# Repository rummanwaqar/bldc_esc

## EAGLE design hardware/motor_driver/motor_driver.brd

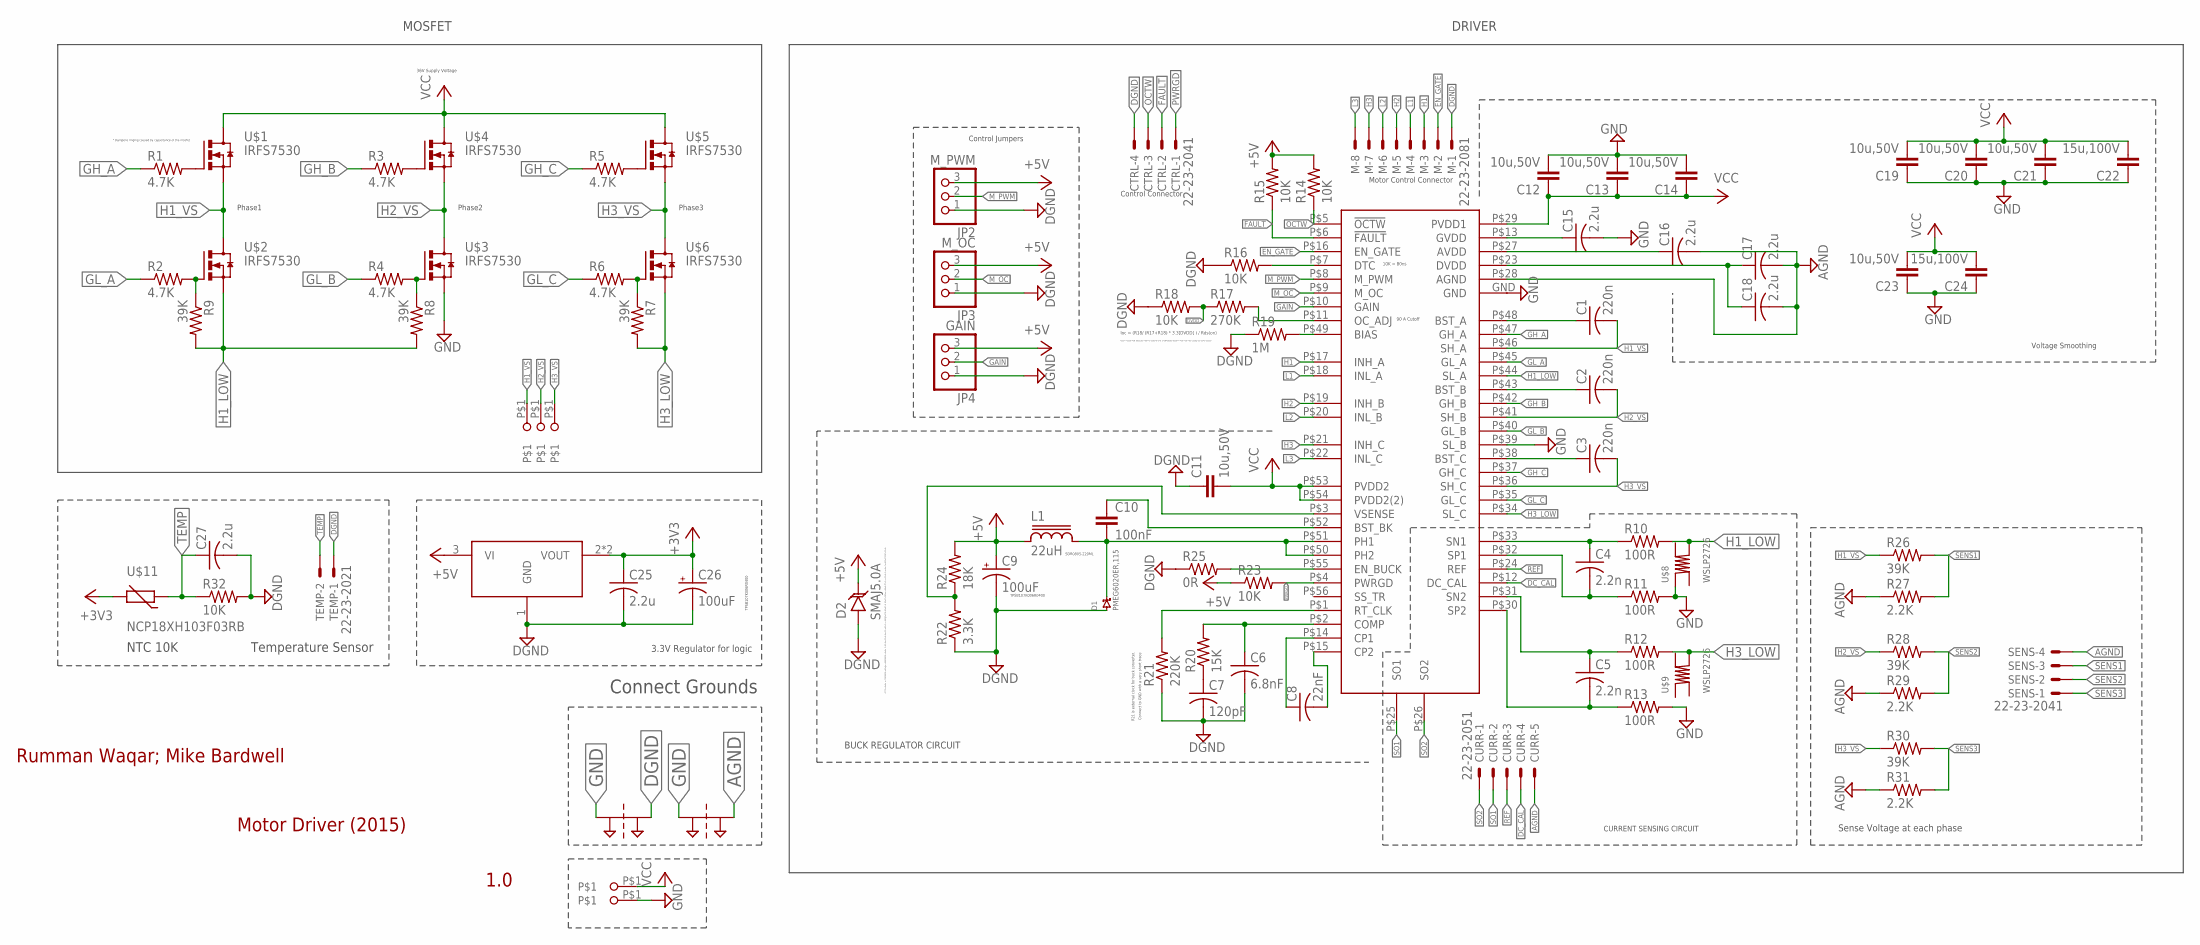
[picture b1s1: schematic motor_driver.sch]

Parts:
C1, C2, C3: 220n; C0805
C4, C5: 2.2n; C0603
C6: 6.8nF; C0603
C7: 120pF; C0603
C8: 22nF; C0603
C9, C26: 100uF; EIA3528-KIT
C10: 100nF; 0805
C11, C12, C13, C14, C19, C20, C21, C23: 10u,50V; 1206
C15, C16, C17, C18, C25, C27: 2.2u; C0805
C22, C24: 15u,100V; C2220K
CTRL: 22-23-2041
CURR: 22-23-2051
D1: PMEG6020ER,115; SOD123W
D2: SMAJ5.0A; SMA-DIODE
JP2: M_PWM; 1X03
JP3: M_OC; 1X03
JP4: GAIN; 1X03
L1: 22uH; SDR0805
M: 22-23-2081
PT1, PT2: 2PT_GND_TIE
R1, R2, R3, R4, R5, R6: 4.7K; R0603
R7, R8, R9: 39K; R0603
R10, R11, R12, R13: 100R; R0603
R14, R15, R16, R18, R23: 10K; R0603
R17: 270K; R0603
R19: 1M; R0603
R20: 15K; R0603
R21: 220K; R0603
R22: 3.3K; R0603
R24: 18K; R0603
R25: 0R; R0603
R26, R28, R30: 39K; R0805
R27, R29, R31: 2.2K; R0805
R32: 10K; M0805
SENS: 22-23-2041
TEMP: 22-23-2021
U$1, U$2, U$3, U$4, U$5, U$6: IRFS7530; IRF7530_HEATSINK
U$7: DRV8302
U$8, U$9: WSLP2726
U$10: TC2117; SOT223
U$11: NCP18XH103F03RB; R0603
U$12, U$13, U$14, U$15, U$16: 1CONN_SOLDER; 1CONN_PAD

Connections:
+3V3: C25.1, C26.A (+), U$10.2 (VOUT), U$10.4 (VOUT), U$11.2
+5V: C9.A (+), D2.C, JP2.3, JP3.3, JP4.3, L1.1, R14.2, R15.2, R23.1, R24.2, U$10.3 (VI)
AGND: C16.2, C17.2, C18.2, CURR.5, PT2.P$2, R27.1, R29.1, R31.1, SENS.4, U$7.P$28 (AGND)
DC_CAL: CURR.4, U$7.P$12 (DC_CAL)
DGND: C6.2, C7.2, C9.C (-), C11.1, C25.2, C26.C (-), C27.2, CTRL.4, D1.P$1 (1), D2.A, JP2.1, JP3.1, JP4.1, M.1, PT1.P$2, R16.1, R18.1, R19.1, R21.1, R22.1, R25.1, R32.2, TEMP.1, U$10.1 (GND)
DVDD: R17.1, R18.2
EN_GATE: M.2, U$7.P$16 (EN_GATE)
FAULT: CTRL.2, R15.1, U$7.P$6 (!FAULT)
GAIN: JP4.2, U$7.P$10 (GAIN)
GH_A: R1.1, U$7.P$47 (GH_A)
GH_B: R3.1, U$7.P$42 (GH_B)
GH_C: R5.1, U$7.P$37 (GH_C)
GL_A: R2.1, U$7.P$45 (GL_A)
GL_B: R4.1, U$7.P$40 (GL_B)
GL_C: R6.1, U$7.P$35 (GL_C)
H1: M.3, U$7.P$17 (INH_A)
H1_VS: C1.2, R26.1, U$1.S1 (S), U$1.S2 (S), U$1.S3 (S), U$1.S4 (S), U$1.S5 (S), U$2.D1 (D), U$7.P$46 (SH_A), U$14.P$1
H2: M.5, U$7.P$19 (INH_B)
H2_VS: C2.2, R28.1, U$3.D1 (D), U$4.S1 (S), U$4.S2 (S), U$4.S3 (S), U$4.S4 (S), U$4.S5 (S), U$7.P$41 (SH_B), U$13.P$1
H3: M.7, U$7.P$21 (INH_C)
H3_VS: C3.2, R30.1, U$5.S1 (S), U$5.S2 (S), U$5.S3 (S), U$5.S4 (S), U$5.S5 (S), U$6.D1 (D), U$7.P$36 (SH_C), U$12.P$1
L1: M.4, U$7.P$18 (INL_A)
L2: M.6, U$7.P$20 (INL_B)
L3: M.8, U$7.P$22 (INL_C)
M_OC: JP3.2, U$7.P$9 (M_OC)
M_PWM: JP2.2, U$7.P$8 (M_PWM)
unnamed: R1.2, U$1.G1 (G)
unnamed: R2.2, R9.1, U$2.G1 (G)
unnamed: R4.2, R8.1, U$3.G1 (G)
unnamed: R3.2, U$4.G1 (G)
unnamed: R5.2, U$5.G1 (G)
unnamed: R6.2, R7.1, U$6.G1 (G)
unnamed: C1.1, U$7.P$48 (BST_A)
unnamed: R17.2, U$7.P$11 (OC_ADJ)
unnamed: C8.1, U$7.P$14 (CP1)
unnamed: C5.2, R13.1, U$7.P$30 (SP2)
unnamed: C2.1, U$7.P$43 (BST_B)
unnamed: C8.2, U$7.P$15 (CP2)
unnamed: C7.1, R20.1
unnamed: R21.2, U$7.P$1 (RT_CLK)
unnamed: R16.2, U$7.P$7 (DTC)
unnamed: R25.2, U$7.P$55 (EN_BUCK)
unnamed: C15.1, U$7.P$13 (GVDD)
unnamed: C10.2, D1.P$2 (2), L1.2, U$7.P$50 (PH2), U$7.P$51 (PH1)
unnamed: C6.1, R20.2, U$7.P$2 (COMP)
unnamed: R19.2, U$7.P$49 (BIAS)
unnamed: C4.1, R10.1, U$7.P$33 (SN1)
unnamed: C4.2, R11.1, U$7.P$32 (SP1)
unnamed: C5.1, R12.1, U$7.P$31 (SN2)
unnamed: C3.1, U$7.P$38 (BST_C)
unnamed: C16.1, U$7.P$27 (AVDD)
unnamed: R22.2, R24.1, U$7.P$3 (VSENSE)
unnamed: C10.1, U$7.P$52 (BST_BK)
unnamed: C17.1, C18.1, U$7.P$23 (DVDD)
OCTW: CTRL.3, R14.1, U$7.P$5 (!OCTW)
PWRGD: CTRL.1, R23.2, U$7.P$4 (PWRGD)
REF: CURR.3, U$7.P$24 (REF)
SENS1: R26.2, R27.2, SENS.3
SENS2: R28.2, R29.2, SENS.2
SENS3: R30.2, R31.2, SENS.1
SO1: CURR.2, U$7.P$25 (SO1)
SO2: CURR.1, U$7.P$26 (SO2)
TEMP: C27.1, R32.1, TEMP.2, U$11.1
VCC: C11.2, C12.1, C13.1, C14.1, C19.2, C20.2, C21.2, C22.2, C23.2, C24.2, U$1.D1 (D), U$4.D1 (D), U$5.D1 (D), U$7.P$29 (PVDD1), U$7.P$53 (PVDD2), U$7.P$54 (PVDD2(2)), U$15.P$1

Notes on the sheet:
* Dampens ringing caused by capacitance of the mosfet
36V Supply Voltage
Phase1
Phase2
Phase3
MOSFET
CURRENT SENSING CIRCUIT
Motor Control Connector
Control Jumpers
10K = 80ns
Ioc = (R18/ (R17+R18) * 3.3[DVDD] ) / Rds(on)
90 A Cutoff
R21 is external clock for buck converter.
Connect to GND with a very short trace.
SDR0805-220ML
TPSB107K006R0400
A TVS diode, or transient voltage suppression diode, is an electrical device which is designed to divert or shunt voltage spikes from a circuit in order to protect that circuit.
BUCK REGULATOR CIRCUIT
Control Connector
Don't mount R18, because internal current limit of DRV8302 doesn't work with this config for some reason
Voltage Smoothing
Sense Voltage at each phase
3.3V Regulator for logic
DRIVER
Rumman Waqar; Mike Bardwell
Motor Driver (2015)
1.0
Connect Grounds
NTC 10K
Temperature Sensor

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
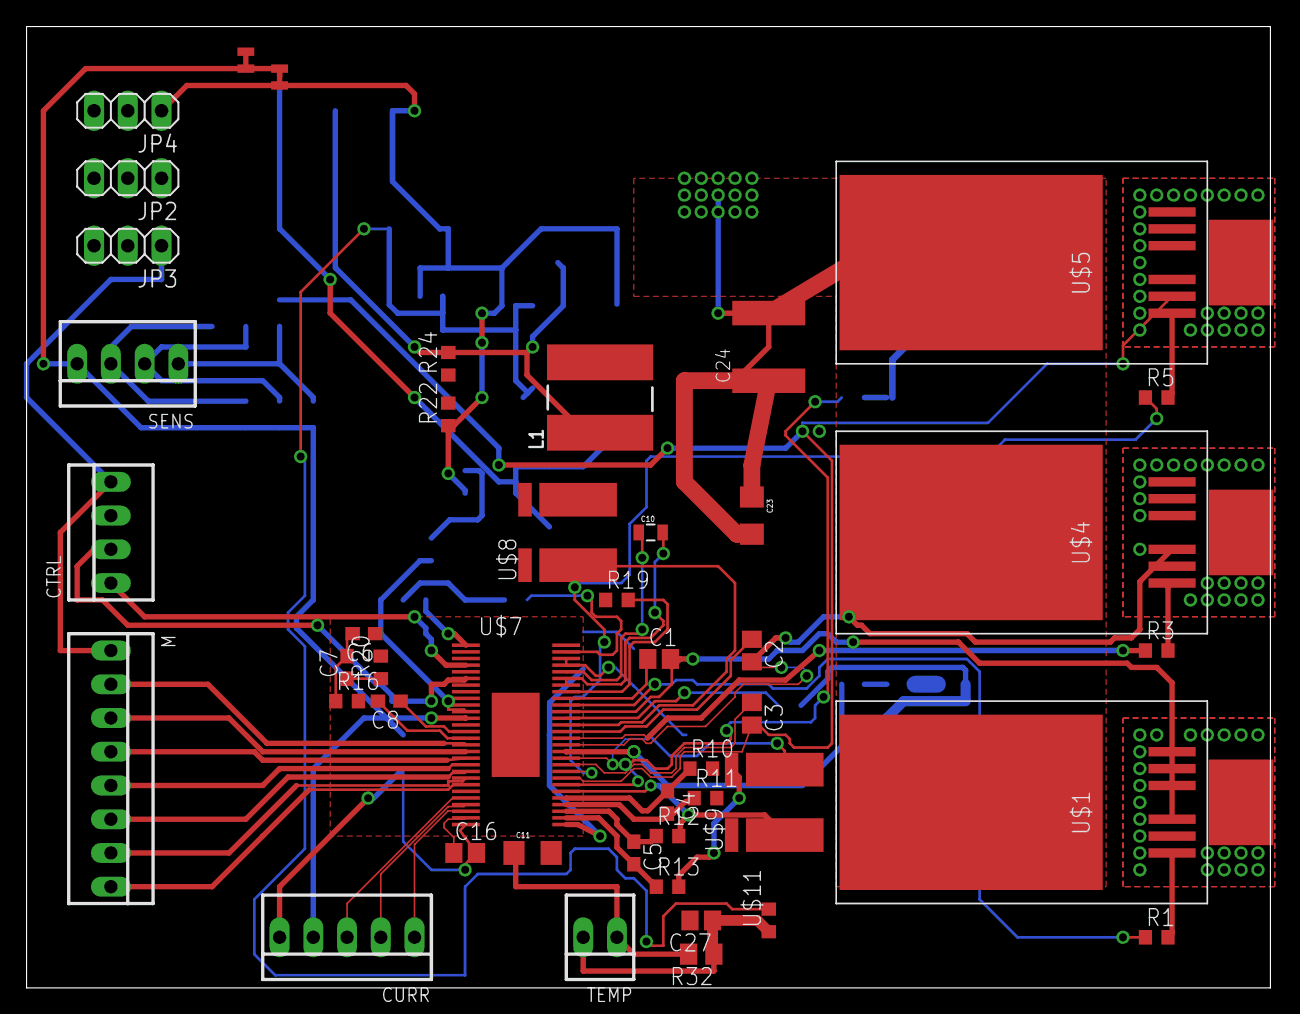
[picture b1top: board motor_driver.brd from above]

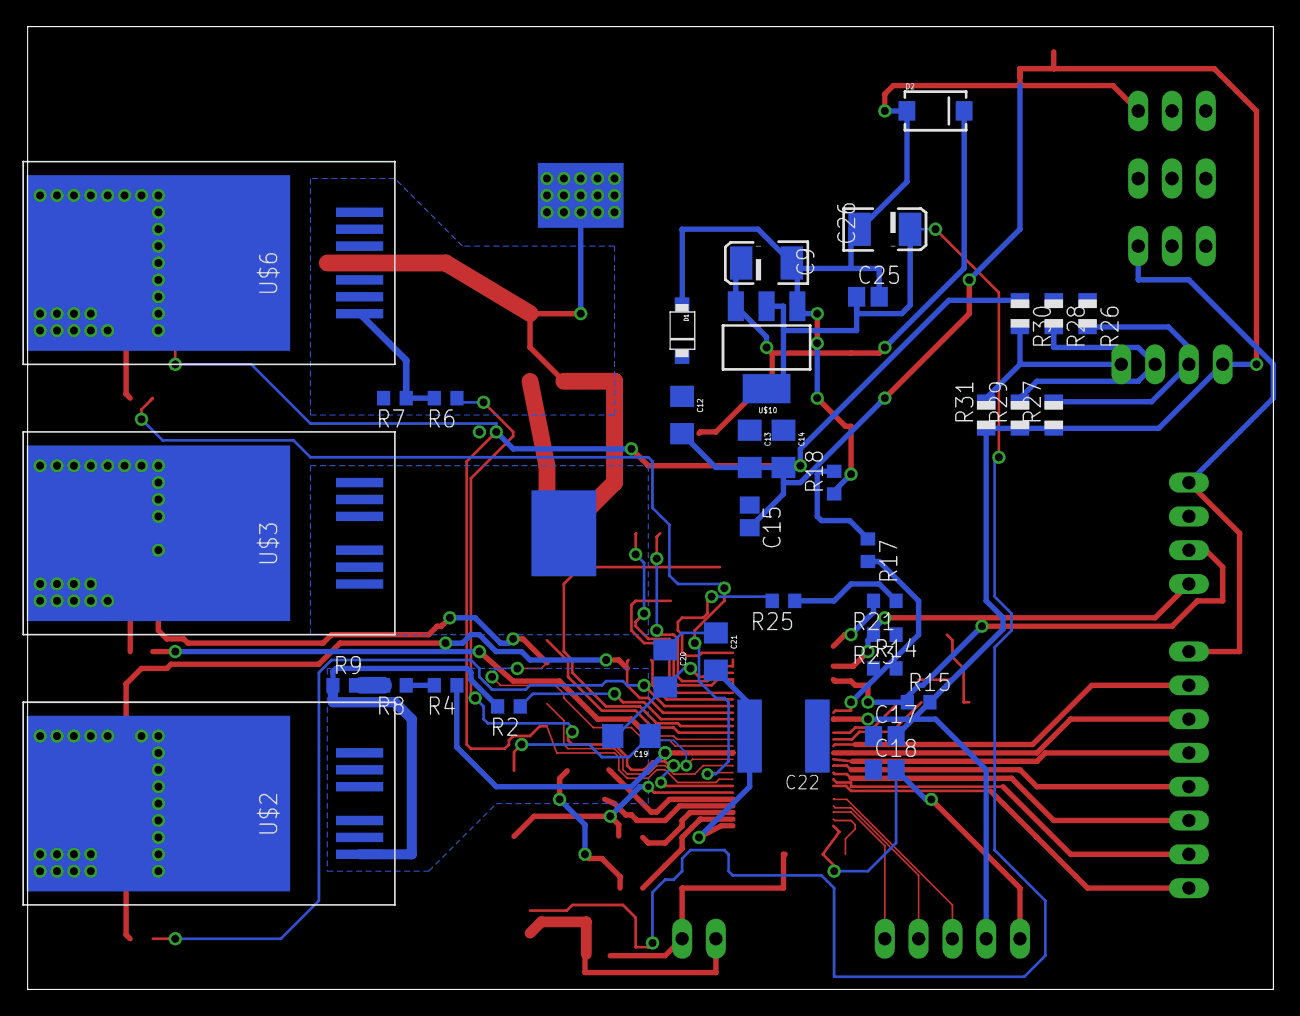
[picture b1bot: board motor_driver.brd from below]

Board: 2 copper layers, 93.7 x 72.4 mm, 88 parts (40 on the bottom side), 71 nets.

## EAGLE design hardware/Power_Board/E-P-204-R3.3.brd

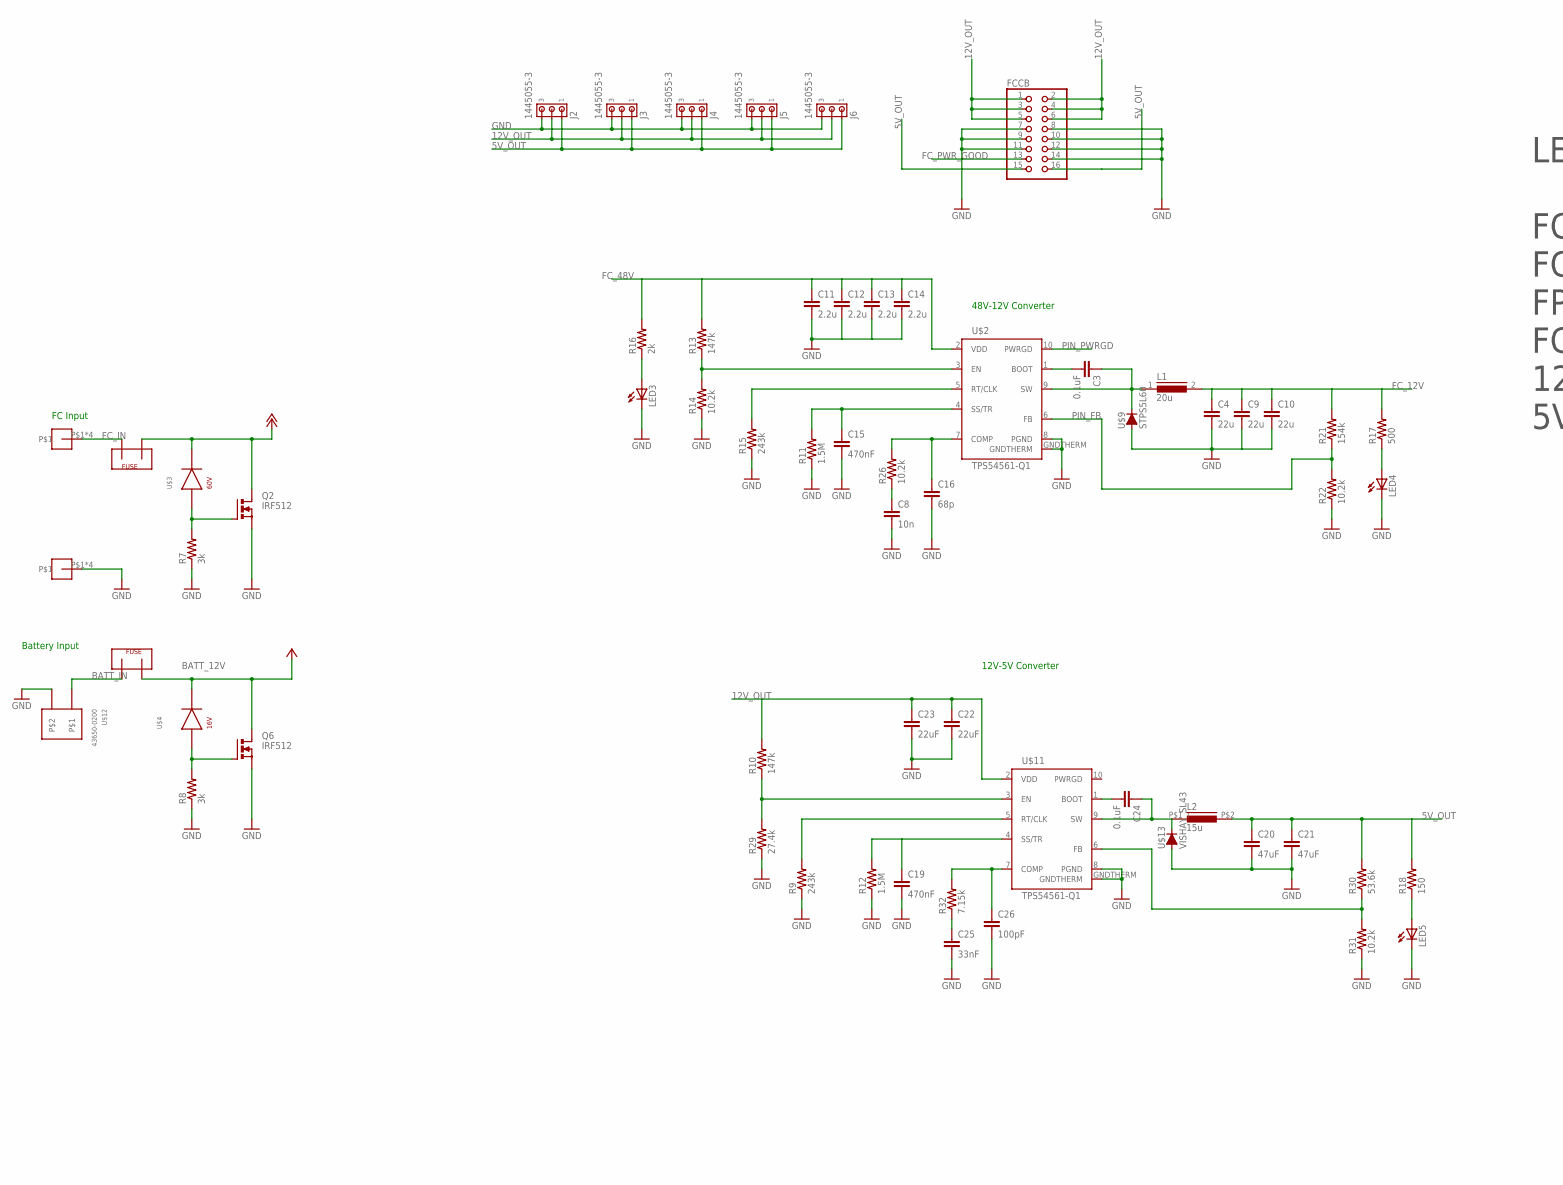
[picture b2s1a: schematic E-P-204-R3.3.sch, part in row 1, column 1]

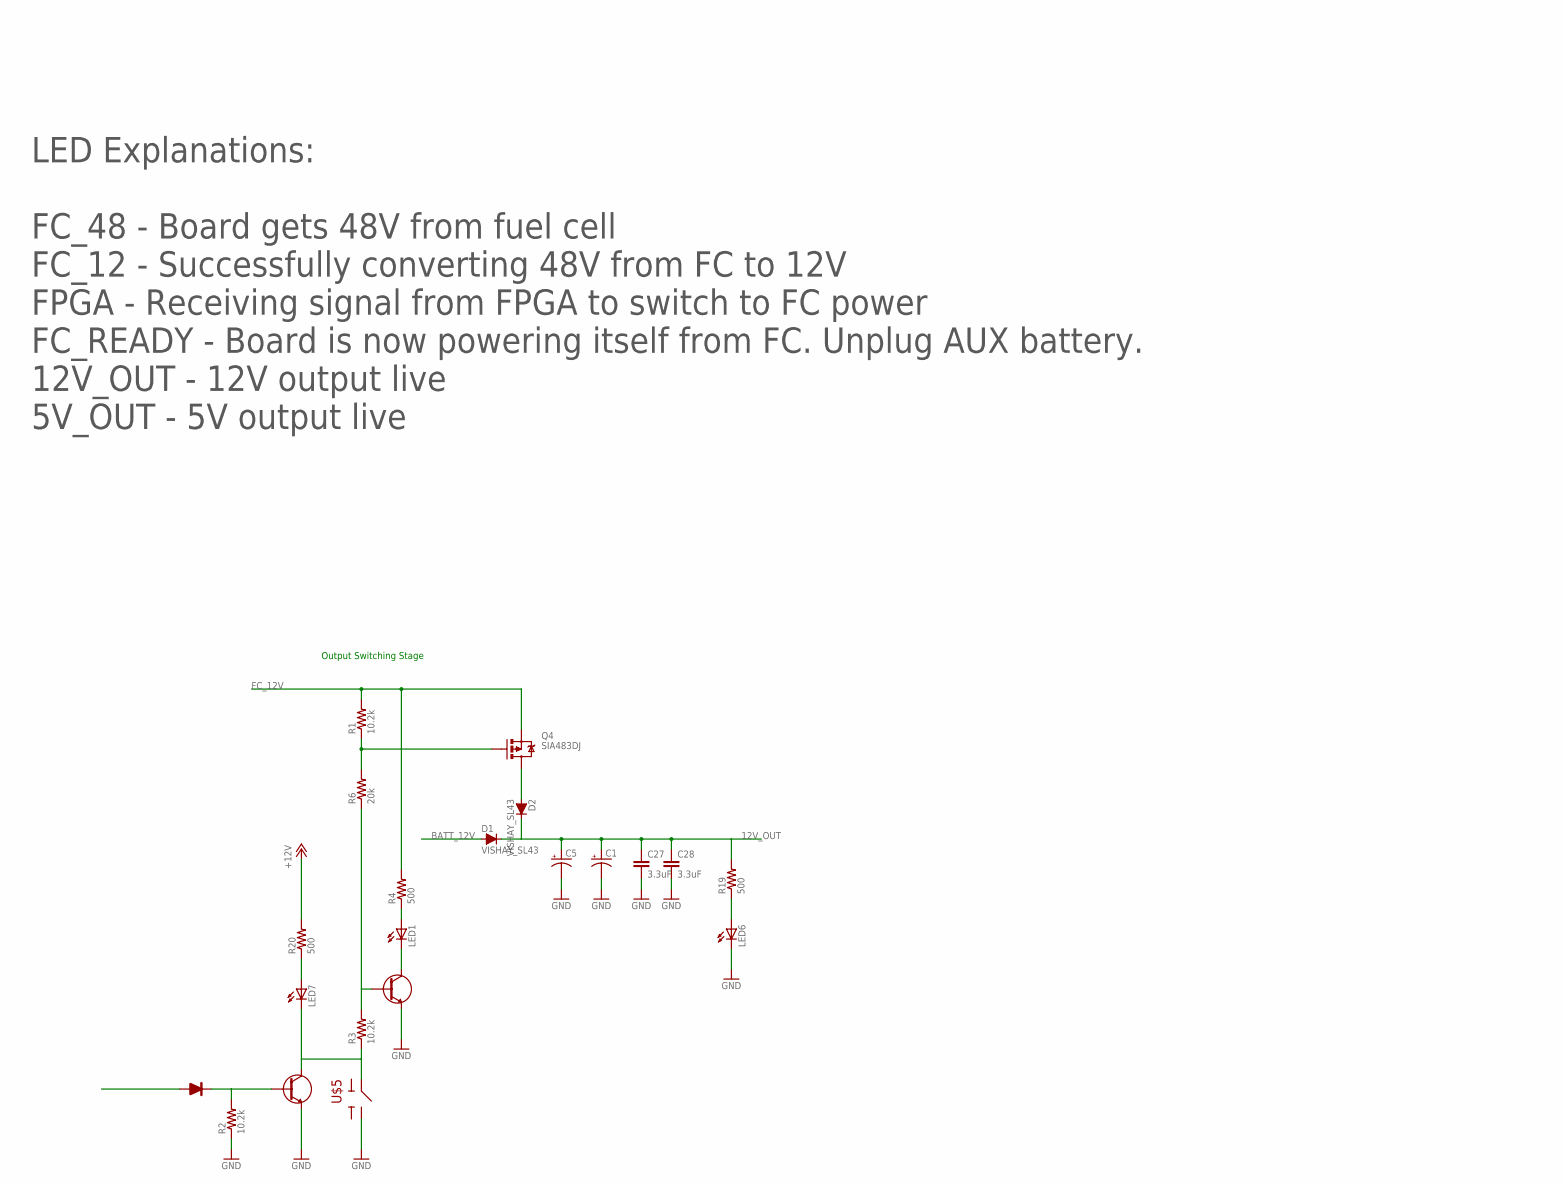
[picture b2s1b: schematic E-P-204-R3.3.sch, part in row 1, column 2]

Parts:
C1, C5: CAP_POLE; PANASONIC_E
C3, C24: 0.1uF; C0603K
C4, C9, C10: 22u; C0805K
C8: 10n; C0805K
C11, C12, C13, C14: 2.2u; 1210
C15, C19: 470nF; C0805K
C16: 68p; C0805K
C20, C21: 47uF; C0805K
C22, C23: 22uF; C0805K
C25: 33nF; C0805K
C26: 100pF; C0805K
C27, C28: 3.3uF; C0805K
D1, D2: VISHAY_SL43; DO-214AB_SMC
FCCB: PINHD-2X8; 2X08
J2, J3, J4, J5, J6: 1445055-3
L1: 20u; CTX-20-5-52R
L2: 15u; DR127
LED1, LED3, LED4, LED5, LED6, LED7: LED1206; LED-1206
Q2, Q6: IRF512; TO220BV
Q4: SIA483DJ; SC70-6L
R1, R2, R3, R14, R22, R26, R31: 10.2k; M0805
R4, R17, R19, R20: 500; M0805
R6: 20k; M0805
R7, R8: 3k; R1210
R9, R15: 243k; M0805
R10, R13: 147k; M0805
R11, R12: 1.5M; M0805
R16: 2k; M0805
R18: 150; M0805
R21: 154k; M0805
R29: 27.4k; M0805
R30: 53.6k; M0805
R32: 7.15k; M0805
U$1, U$14: ZXTN19100CFF; SOT23
U$2, U$11: TPS54561-Q1; PWSON10
U$3: SMBJ60CA; .277X.089
U$4: SMAJ16CA; .25X.07
U$5: GT12MSCBE
U$6, U$8: SCREW-8191
U$7, U$10: FUSEMINI-BLADE; MINI-BLADE-FUSE
U$9: STPS5L60; STM_SMC
U$12: 43650-0200
U$13: VISHAY_SL43; DO-214AB_SMC
U$15: CDSF4148

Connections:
5V_OUT: C20.1, C21.1, FCCB.15, FCCB.16, J2.1, J3.1, J4.1, J5.1, J6.1, L2.P$2 (2), R18.2, R30.2
12V_OUT: C1.+, C5.+, C22.1, C23.1, C27.1, C28.1, D1.C, D2.C, FCCB.1, FCCB.2, FCCB.3, FCCB.4, FCCB.5, FCCB.6, J2.2, J3.2, J4.2, J5.2, J6.2, R10.2, R19.2, R20.2, U$11.2 (VDD)
BATT_12V: D1.A, Q6.D, U$4.CATHODE, U$10.IN
BATT_IN: U$10.OUT, U$12.P$2
FC_12V: C4.1, C9.1, C10.1, L1.2, Q4.S@0 (S), Q4.S@1 (S), R1.2, R4.2, R17.2, R21.2
FC_48V: C11.1, C12.1, C13.1, C14.1, Q2.D, R13.2, R16.2, U$2.2 (VDD), U$3.CATHODE, U$7.OUT
FC_IN: U$7.IN, U$8.P$1, U$8.P$2, U$8.P$3, U$8.P$4
FC_PWR_GOOD: FCCB.13, U$15.ANODE (P$A)
GND: C1.-, C4.2, C5.-, C8.2, C9.2, C10.2, C11.2, C12.2, C13.2, C14.2, C15.2, C16.2, C19.2, C20.2, C21.2, C22.2, C23.2, C25.2, C26.2, C27.2, C28.2, FCCB.7, FCCB.8, FCCB.9, FCCB.10, FCCB.11, FCCB.12, FCCB.14, J2.3, J3.3, J4.3, J5.3, J6.3, LED3.C, LED4.C, LED5.C, LED6.C, Q2.S, Q6.S, R2.1, R7.1, R8.1, R9.1, R11.1, R12.1, R14.1, R15.1, R22.1, R29.1, R31.1, U$1.P$2E (P$E), U$2.8 (PGND), U$2.GNDTHERM, U$5.P$3, U$6.P$1, U$6.P$2, U$6.P$3, U$6.P$4, U$9.A, U$11.8 (PGND), U$11.GNDTHERM, U$12.P$1, U$13.A, U$14.P$2E (P$E)
unnamed: C3.2, U$2.1 (BOOT)
unnamed: R9.2, U$11.5 (RT/CLK)
unnamed: LED7.C, R3.1, U$5.P$1, U$14.P$3C (P$C)
unnamed: R3.2, R6.1, U$1.P$1B (P$B)
unnamed: C3.1, L1.1, U$2.9 (SW), U$9.C
unnamed: Q4.G, R1.1, R6.2
unnamed: Q2.G, R7.2, U$3.ANODE
unnamed: Q6.G, R8.2, U$4.ANODE
unnamed: D2.A, Q4.D
unnamed: R13.1, R14.2, U$2.3 (EN)
unnamed: LED1.C, U$1.P$3C (P$C)
unnamed: R10.1, R29.2, U$11.3 (EN)
unnamed: R15.2, U$2.5 (RT/CLK)
unnamed: LED1.A, R4.1
unnamed: R2.2, U$14.P$1B (P$B), U$15.CATHODE (P$C)
unnamed: C16.1, R26.2, U$2.7 (COMP)
unnamed: LED3.A, R16.1
unnamed: LED4.A, R17.1
unnamed: LED5.A, R18.1
unnamed: C8.1, R26.1
unnamed: LED6.A, R19.1
unnamed: C19.1, R12.2, U$11.4 (SS/TR)
unnamed: C24.2, U$11.1 (BOOT)
unnamed: LED7.A, R20.1
unnamed: C24.1, L2.P$1 (1), U$11.9 (SW), U$13.C
unnamed: R30.1, R31.2, U$11.6 (FB)
unnamed: C26.1, R32.2, U$11.7 (COMP)
unnamed: C25.1, R32.1
PIN_FB: R21.1, R22.2, U$2.6 (FB)
PIN_PWRGD: U$2.10 (PWRGD)
PIN_SS: C15.1, R11.2, U$2.4 (SS/TR)

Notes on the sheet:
Output Switching Stage
Battery Input
FC Input
48V-12V Converter
12V-5V Converter
LED Explanations: FC_48 - Board gets 48V from fuel cell FC_12 - Successfully converting 48V from FC to 12V FPGA - Receiving signal from FPGA to switch to FC power FC_READY - Board is now powering itself from FC. Unplug AUX battery. 12V_OUT - 12V output live 5V_OUT - 5V output live

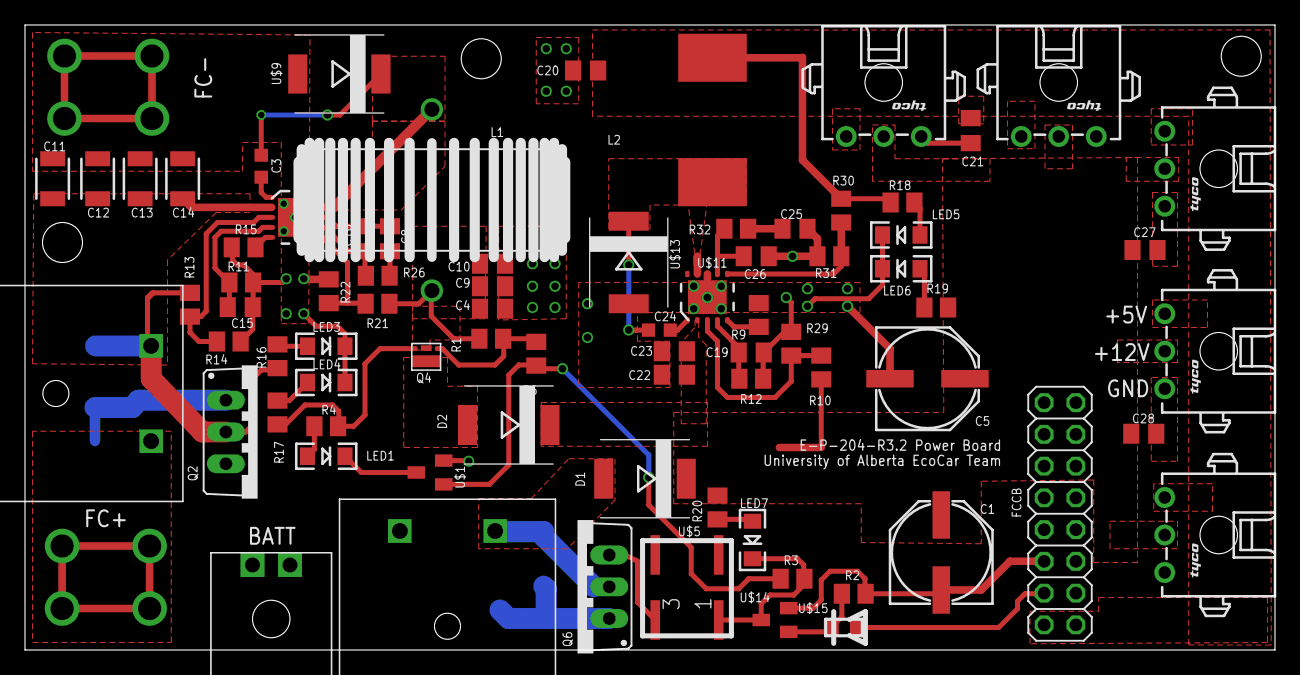
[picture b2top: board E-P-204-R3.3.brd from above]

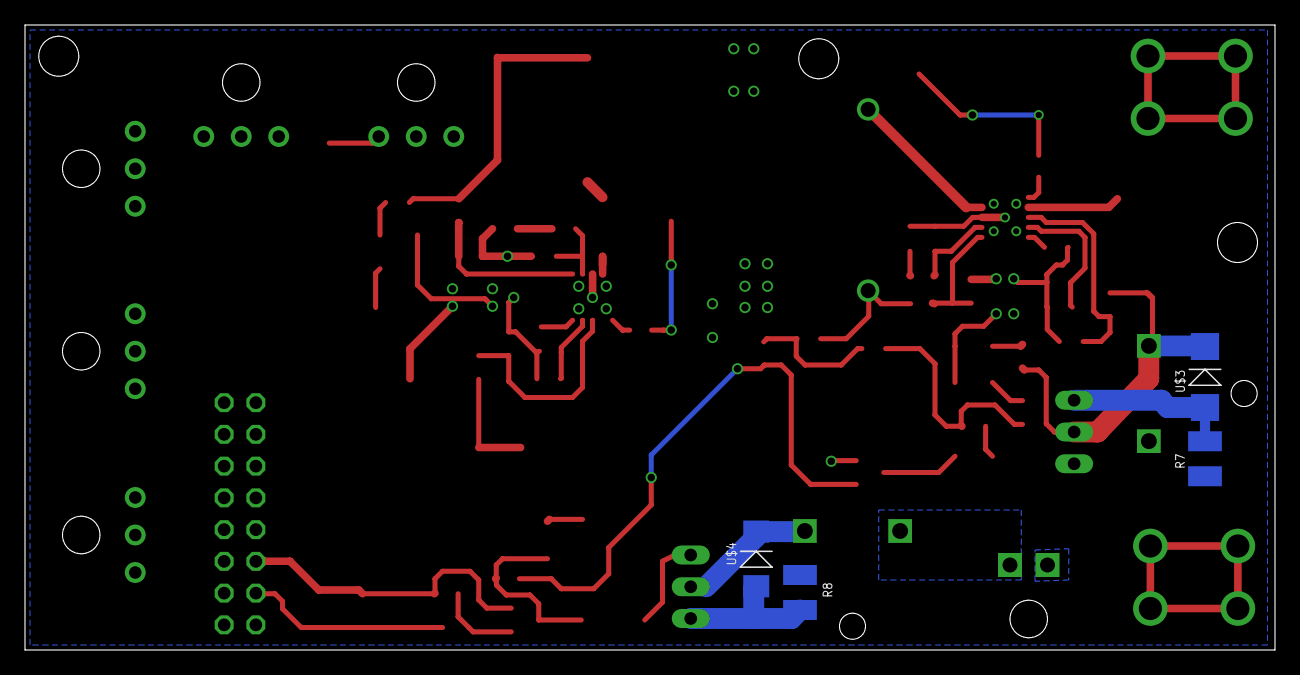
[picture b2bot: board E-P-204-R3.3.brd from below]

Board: 2 copper layers, 100.0 x 50.0 mm, 83 parts (4 on the bottom side), 39 nets.

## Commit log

2015-07-29 Added gitignore
2015-07-29 added schematic for motor driver
2015-07-29 added library for MOSFET + Heatsink array
2015-07-29 added MOSFET driver to library
2015-07-31 updating motor driver design 30/07/15
2015-08-03 Updated motor controller schematic, driver almost done but components (caps, ind, res) packages still need to be spec'd out
2015-08-03 Finished driver and MOSFET's external connections. Package choices still need to be reviewed
2015-08-03 started board layout
2015-08-04 Changed 0603 layout a bit to centre the alignment mark
2015-08-14 no change made
2015-08-20 Full Motor Driver updates and first in depth review of the board
2015-08-22 Pushing library updates
2015-08-22 redid the sch
2015-08-22 Made changes
2015-08-23 Added new libraries
2015-08-23 Completed first revision of design
2015-08-23 fixing multplie library folders
2015-08-23 new library folder
2015-08-23 Added temperature sensor
2015-08-23 Added connectors for motor and power
2015-08-23 Fixed mosfet package origin
2015-08-24 Grounded MOSFETS
2015-08-24 Fixed Solder Connector footprint
2015-08-24 Layout of components
2015-09-13 Made the changes mike suggested
2015-09-13 First commit on Mike's branch. Starting board layout. Rumman is doing the same.
2015-09-13 Board route (manual) trial number 1
2015-09-13 small change
2015-09-14 Routed mosfets
2015-09-15 more mosfet stuff
2015-09-22 Shit from Sunday work session
2015-09-22 more board layout done, still need to fix resistor package
2015-09-23 Fixed some of the spacing issues aroud the Driver
2015-09-26 Changed shunt resistor sch, needs confirmtion
2015-09-26 Almost there
2015-10-10 Added Up to date board with ~300 clearence and overlap issues to be opened as a challenge to the general EcoCar Team
2015-11-22 added pictures for historical purposes

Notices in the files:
parts and their libraries:
SparkFun: Licensing: CC v3.0 Share-Alike You are welcome to use this library for commercial purposes.
SparkFun-Passives: Licensing: Creative Commons ShareAlike 4.0 International - https://creativecommons.org/licenses/by-sa/4.0
bourne: Copyright (C) 2008, Bob Starr
